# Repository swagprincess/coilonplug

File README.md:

# Dwell converter board

This board lets you use a Toyota/Audi/etc "coil on plug" ignition system with the stock ecu in a Mazda MX5/Miata (1989-2005).

The board will take in a variable dwell signal for the stock coilpack and output a (falling edge synchronised) stable, adjustable dwell pulse.

Current setting is 70 "ticks" of TIMER1, around 2.2ms, correct for Toyota COP's at running voltages (should be good for Audi R8 coils too).

Written in C for an AtTiny84A.

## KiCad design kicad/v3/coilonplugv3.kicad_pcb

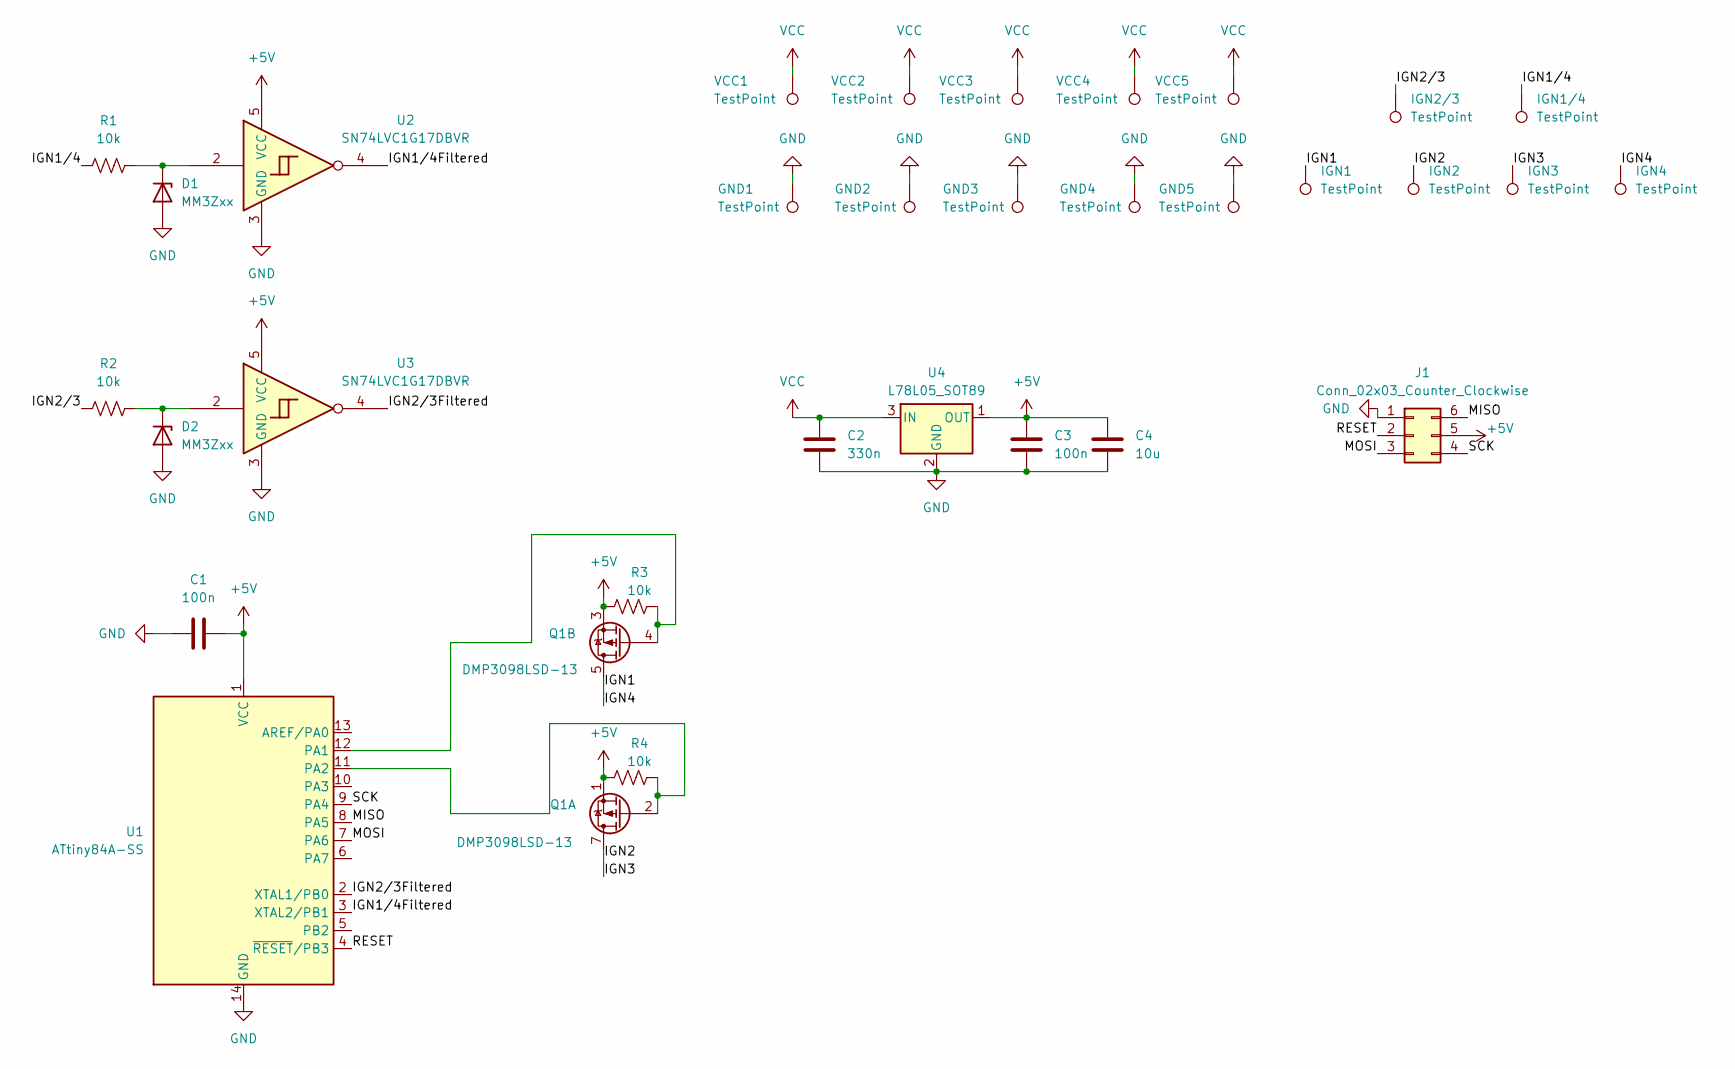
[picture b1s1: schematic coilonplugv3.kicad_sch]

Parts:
C1, C3: 100n; C_0603_1608Metric; LCSC Part # C77055
C2: 330n; C_0603_1608Metric; LCSC Part # C354382
C4: 10u; C_0603_1608Metric; LCSC Part # C2959727
D1, D2: MM3Zxx; D_SOD-323F; LCSC Part # C154578
GND1, GND2, GND3, GND4, GND5: TestPoint; TestPoint_Pad_2.5x2.5mm
IGN1, IGN1/4, IGN2, IGN2/3, IGN3, IGN4: TestPoint; TestPoint_Pad_2.5x2.5mm
J1: Conn_02x03_Counter_Clockwise; PinHeader_2x03_P2.54mm_Vertical; LCSC Part # C2764576
Q1: DMP3098LSD-13; SOIC-8_3.9x4.9mm_P1.27mm; LCSC Part # C531177
R1, R2, R3, R4: 10k; R_0603_1608Metric; LCSC Part # C116677
U1: ATtiny84A-SS; SOIC-14_3.9x8.7mm_P1.27mm; LCSC Part # C1340034
U2, U3: SN74LVC1G17DBVR; SOT-23-5; LCSC Part # C7836
U4: L78L05_SOT89; SOT-89-3; LCSC Part # C42738
VCC1, VCC2, VCC3, VCC4, VCC5: TestPoint; TestPoint_Pad_2.5x2.5mm

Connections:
+5V: C1.1, C3.1, C4.1, J1.5, Q1.1 (S1), Q1.3 (S2), R3.2, R4.2, U1.1 (VCC), U2.5 (VCC), U3.5 (VCC), U4.1 (OUT)
/IGN1: IGN1.1 (1_1), IGN4.1 (1_1), Q1.5 (D2), Q1.6 (D2)
/IGN1/4: IGN1/4.1 (1_1), R1.1
/IGN1/4Filtered: U1.3 (XTAL2/PB1), U2.4
/IGN2: IGN2.1 (1_1), IGN3.1 (1_1), Q1.7 (D1), Q1.8 (D1)
/IGN2/3: IGN2/3.1 (1_1), R2.1
/IGN2/3Filtered: U1.2 (XTAL1/PB0), U3.4
/MISO: J1.6, U1.8 (PA5)
/MOSI: J1.3, U1.7 (PA6)
/RESET: J1.2, U1.4 (~RESET/PB3)
/SCK: J1.4, U1.9 (PA4)
GND: C1.2, C2.2, C3.2, C4.2, D1.2 (A), D2.2 (A), GND1.1 (1_1), GND2.1 (1_1), GND3.1 (1_1), GND4.1 (1_1), GND5.1 (1_1), J1.1, U1.14 (GND), U2.3 (GND), U3.3 (GND), U4.2 (GND)
unnamed: D1.1 (K), R1.2, U2.2
unnamed: D2.1 (K), R2.2, U3.2
unnamed: Q1.2 (G1), R4.1, U1.11 (PA2)
unnamed: Q1.4 (G2), R3.1, U1.12 (PA1)
VCC: C2.1, U4.3 (IN), VCC1.1 (1_1), VCC2.1 (1_1), VCC3.1 (1_1), VCC4.1 (1_1), VCC5.1 (1_1)

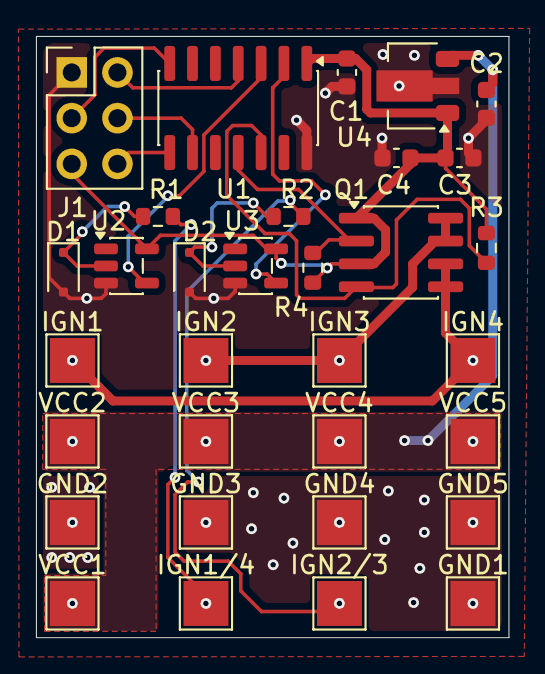
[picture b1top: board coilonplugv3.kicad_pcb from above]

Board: 2 copper layers, 26.2 x 33.4 mm, 32 parts (0 on the bottom side), 17 nets.

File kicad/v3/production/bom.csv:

Designator,Footprint,Quantity,Value,LCSC Part #
"C1, C3",0603,2,100n,C77055
C2,0603,1,330n,C354382
C4,0603,1,10u,C2959727
"D1, D2",D_SOD-323F,2,MM3Zxx,C154578
Q1,SOIC-8_3.9x4.9mm_P1.27mm,1,DMP3098LSD-13,C531177
"R1, R2, R3, R4",0603,4,10k,C116677
U1,SOIC-14_3.9x8.7mm_P1.27mm,1,ATtiny84A-SS,C1340034
"U2, U3",SOT-23-5,2,SN74LVC1G17DBVR,C7836
U4,SOT-89-3,1,L78L05_SOT89,C42738

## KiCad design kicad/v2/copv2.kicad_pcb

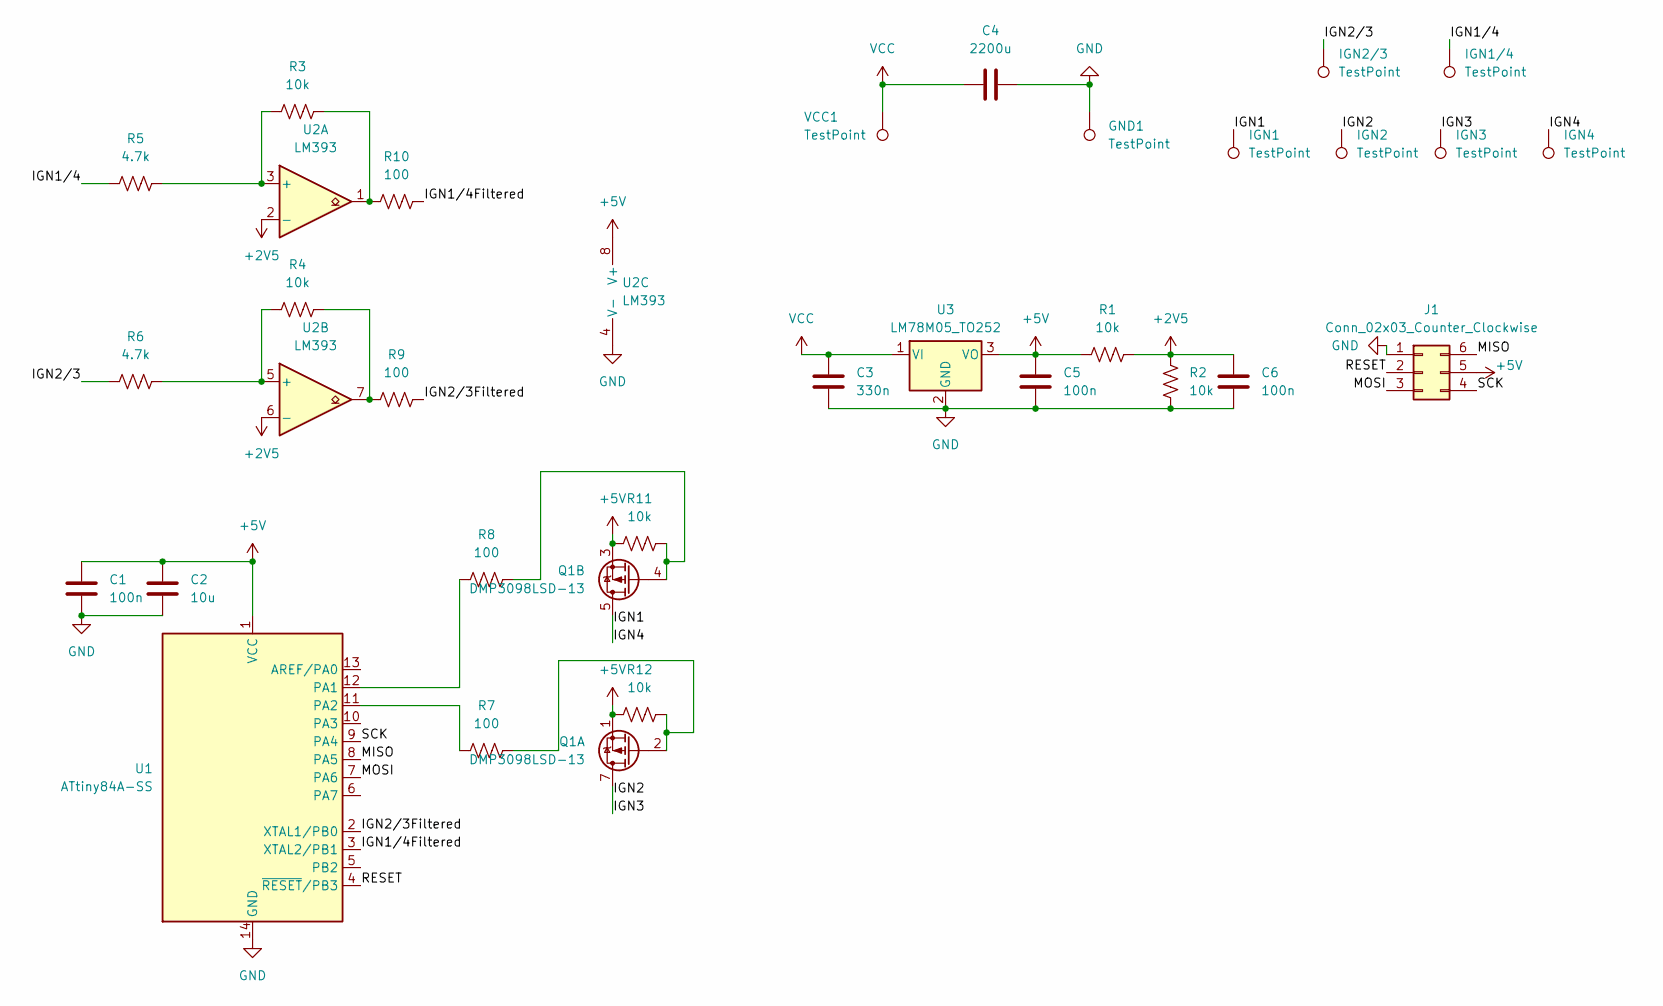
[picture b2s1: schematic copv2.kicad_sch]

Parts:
C1, C5, C6: 100n; C_0603_1608Metric; LCSC Part # C77055
C2: 10u; C_0603_1608Metric; LCSC Part # C2959727
C3: 330n; C_0603_1608Metric; LCSC Part # C107070
C4: 2200u; CP_Radial_D12.5mm_P5.00mm; LCSC Part # C111500
GND1: TestPoint; TestPoint_Pad_4.0x4.0mm
IGN1, IGN1/4, IGN2, IGN2/3, IGN3, IGN4: TestPoint; TestPoint_Pad_4.0x4.0mm
J1: Conn_02x03_Counter_Clockwise; PinHeader_2x03_P2.54mm_Vertical; LCSC Part # C2764576
Q1: DMP3098LSD-13; SOIC-8_3.9x4.9mm_P1.27mm; LCSC Part # C531177
R1, R2, R3, R4, R11, R12: 10k; R_0603_1608Metric; LCSC Part # C98220
R5, R6: 4.7k; R_0603_1608Metric; LCSC Part # C116697
R7, R8, R9, R10: 100; R_0603_1608Metric; LCSC Part # C105588
U1: ATtiny84A-SS; SOIC-14_3.9x8.7mm_P1.27mm; LCSC Part # C1340034
U2: LM393; SOIC-8_3.9x4.9mm_P1.27mm; LCSC Part # C32901
U3: LM78M05_TO252; TO-252-2; LCSC Part # C58069
VCC1: TestPoint; TestPoint_Pad_4.0x4.0mm

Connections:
+2V5: C6.1, R1.2, R2.2, U2.2 (-), U2.6 (-)
+5V: C1.1, C2.1, C5.1, J1.5, Q1.1 (S1), Q1.3 (S2), R1.1, R11.2, R12.2, U1.1 (VCC), U2.8 (V+), U3.3 (VO)
/IGN1: IGN1.1, IGN4.1, Q1.5 (D2), Q1.6 (D2)
/IGN1/4: IGN1/4.1, R5.1
/IGN1/4Filtered: R10.1, U1.3 (XTAL2/PB1)
/IGN2: IGN2.1, IGN3.1, Q1.7 (D1), Q1.8 (D1)
/IGN2/3: IGN2/3.1, R6.1
/IGN2/3Filtered: R9.1, U1.2 (XTAL1/PB0)
/MISO: J1.6, U1.8 (PA5)
/MOSI: J1.3, U1.7 (PA6)
/RESET: J1.2, U1.4 (~RESET/PB3)
/SCK: J1.4, U1.9 (PA4)
GND: C1.2, C2.2, C3.2, C4.1, C5.2, C6.2, GND1.1, J1.1, R2.1, U1.14 (GND), U2.4 (V-), U3.2 (GND); also elsewhere on the board
unnamed: Q1.2 (G1), R7.2, R12.1
unnamed: Q1.4 (G2), R8.1, R11.1
unnamed: R4.2, R9.2, U2.7
unnamed: R3.2, R10.2, U2.1
unnamed: R8.2, U1.12 (PA1)
unnamed: R7.1, U1.11 (PA2)
unnamed: R3.1, R5.2, U2.3 (+)
unnamed: R4.1, R6.2, U2.5 (+)
VCC: C3.1, C4.2, U3.1 (VI), VCC1.1; also elsewhere on the board

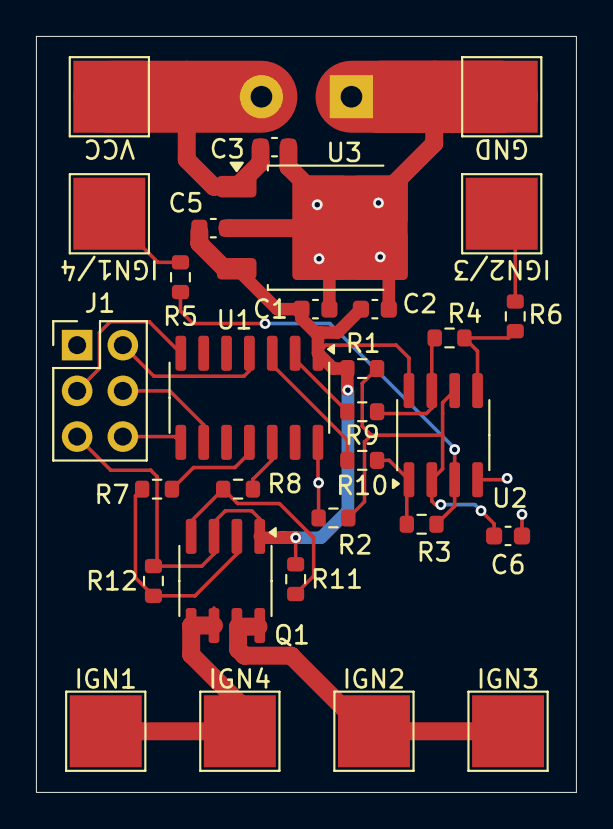
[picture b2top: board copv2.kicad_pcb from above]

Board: 2 copper layers, 30.0 x 42.0 mm, 31 parts (1 on the bottom side), 22 nets.

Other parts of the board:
GND: TestPoint; TestPoint_Pad_4.0x4.0mm
VCC: TestPoint; TestPoint_Pad_4.0x4.0mm

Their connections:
GND: GND.1; also elsewhere on the board
VCC: VCC.1; also elsewhere on the board

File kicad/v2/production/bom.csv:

Designator,Footprint,Quantity,Value,LCSC Part #
"C1, C5, C6",0603,3,100n,C77055
C2,0603,1,10u,C2959727
C3,0603,1,330n,C107070
C4,CP_Radial_D12.5mm_P5.00mm,1,2200u,C111500
Q1,SOIC-8_3.9x4.9mm_P1.27mm,1,DMP3098LSD-13,C531177
"R1, R11, R12, R2, R3, R4",0603,6,10k,C98220
"R10, R7, R8, R9",0603,4,100,C105588
"R5, R6",0603,2,4.7k,C116697
U1,SOIC-14_3.9x8.7mm_P1.27mm,1,ATtiny84A-SS,C1340034
U2,SOIC-8_3.9x4.9mm_P1.27mm,1,LM393,C32901
U3,TO-252-2,1,LM78M05_TO252,C58069

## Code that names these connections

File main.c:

#define F_CPU 8000000UL

#include <avr/io.h>
#include <util/delay.h>
#include <avr/interrupt.h>

#define true 1
#define false 0

volatile uint16_t delayBeforeLow = 50; //ticks at 8mhz prescaler 256, assume 4ms base pulse and 2.4ms wanted
volatile int16_t tempDelayCalc = 0;
volatile uint16_t startTime14 = 0;
volatile uint16_t startTime23 = 0;
volatile uint8_t lastStatePB0 = false;
volatile uint8_t lastStatePB1 = false;
volatile uint8_t set23Low = false;
volatile uint8_t set14Low = false;


ISR(PCINT1_vect){ // interrupt for all port b pins

    cli(); //disable interrupts to avoid infinite loops and 16 bit on 8 bit cpu nonsense

    if (!(PINB & (1 << PB1)) && lastStatePB1){    //IGN 1 & 4
        // PB1 is LOW, turn off PA2 (1 & 4)
        PORTA |= (1 << PA2); // set high for off

        tempDelayCalc = TCNT1 - startTime14 - 75; //2.4ms setting

        if (tempDelayCalc >= 0){
            delayBeforeLow = tempDelayCalc;
        } else {
            delayBeforeLow = 0;
        }

        lastStatePB1 = false;

    } else if ((PINB & (1 << PB1)) && !lastStatePB1) {   //IGN 1 & 4
        // PB1 is HIGH
        startTime14 = TCNT1; // set timer timestamp

        set14Low = true; // mark pin as has to go low eventually 

        lastStatePB1 = true;

    }


    if (!(PINB & (1 << PB0)) && lastStatePB0){    //IGN 2 & 3
        // PB0 is LOW, turn off PA1 (2 & 3)
        PORTA |= (1 << PA1); // set high for off

        tempDelayCalc = TCNT1 - startTime23 - 75; //2.4ms setting

        if (tempDelayCalc >= 0){
            delayBeforeLow = tempDelayCalc;
        } else {
            delayBeforeLow = 0;
        }

        lastStatePB0 = false;

    } else if ((PINB & (1 << PB0)) && !lastStatePB0) {   //IGN 2 & 3
        // PB0 is HIGH 
        startTime23 = TCNT1; // set timer timestamp

        set23Low = true; // mark pin as has to go low eventually 

        lastStatePB0 = true;

    }

    sei(); //enable again
     
}


int main(void) {

    //set output pins as output and set high
    DDRA |= ((1 << DDA1) | (1<< DDA2));
    PORTA |= ((1 << PA1) | (1 << PA2));

    //set input pins as input
    DDRB &= ~((1 << DDB0) | (1 << DDB1));

    TCCR1B = 0; // stop timer

    TCCR1B |= (1 << CS12); // start timer at prescaler 256

    GIMSK |= (1 << PCIE1); //enable group 1 pin interrupts
    PCMSK1 |= (1 << PCINT8) | (1 << PCINT9); // allow pins to trigger interrupt

    sei(); //enable interrupts


    while (1){
        if (set23Low){
            cli(); //16 bit math and time sensitive stuff
            if ((uint16_t)(TCNT1 - startTime23) >= delayBeforeLow){
                PORTA &= ~(1 << PA1); // set low to start trigger
                set23Low = false;
            }
            sei(); //enable interrupts
        }
        if (set14Low){
            cli(); //16 bit math and time sensitive stuff
            if ((uint16_t)(TCNT1 - startTime14) >= delayBeforeLow){
                PORTA &= ~(1 << PA2); // set low to start trigger
                set14Low = false;
            }
            sei(); //enable interrupts
        }
    }

}

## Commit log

2025-08-10 create file
2025-08-10 first complete code to test + makefile
2025-08-10 fix bunch of bs lol
2025-08-10 noise proofing ig
2025-08-10 fix bug with negative delays
2025-08-10 wrong comparison lol
2025-08-10 shhh
2025-08-11 swag
2025-08-11 fix base pulse delay
2025-08-11 kicad added
2025-08-11 bleh
2025-08-11 add cap on 2.5V
2025-08-11 added vias around new capacitor
2025-08-14 fix stuff idk
2025-08-14 move via slightly
2025-08-30 working I think bleh, tested
2025-09-02 code done for now
2025-09-02 mosfet wrong way around
2025-09-02 cranking longer pulse test
2025-09-09 pictures
2025-09-11 testing passthrough pulse length for first 30 events
2025-11-14 change output pins for new pcb revision
2026-05-28 inital desgin of v3 completed
2026-05-28 small pcb changes + get code from latest pcb made
2026-05-28 code optimizations to be tested
2026-05-28 remove makefile from languages
2026-05-29 code optimizations to test
2026-05-29 test failed, try new code
2026-05-29 found bug and fixed maybe
2026-05-29 verified code working on v2 board, to be tested on v3 when ordered
2026-05-30 capacitor brand change before order
2026-05-30 ordered! state of repository when pcb ordered
